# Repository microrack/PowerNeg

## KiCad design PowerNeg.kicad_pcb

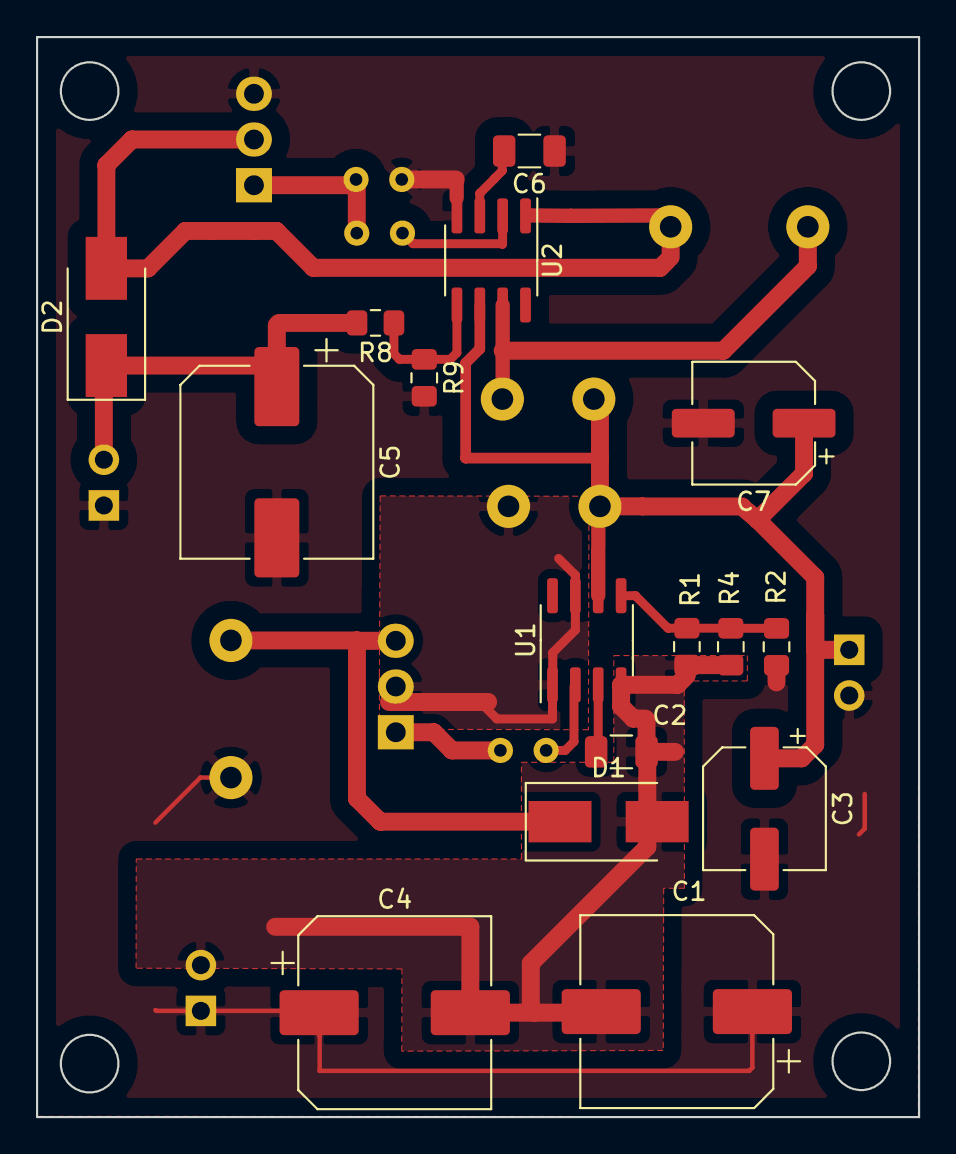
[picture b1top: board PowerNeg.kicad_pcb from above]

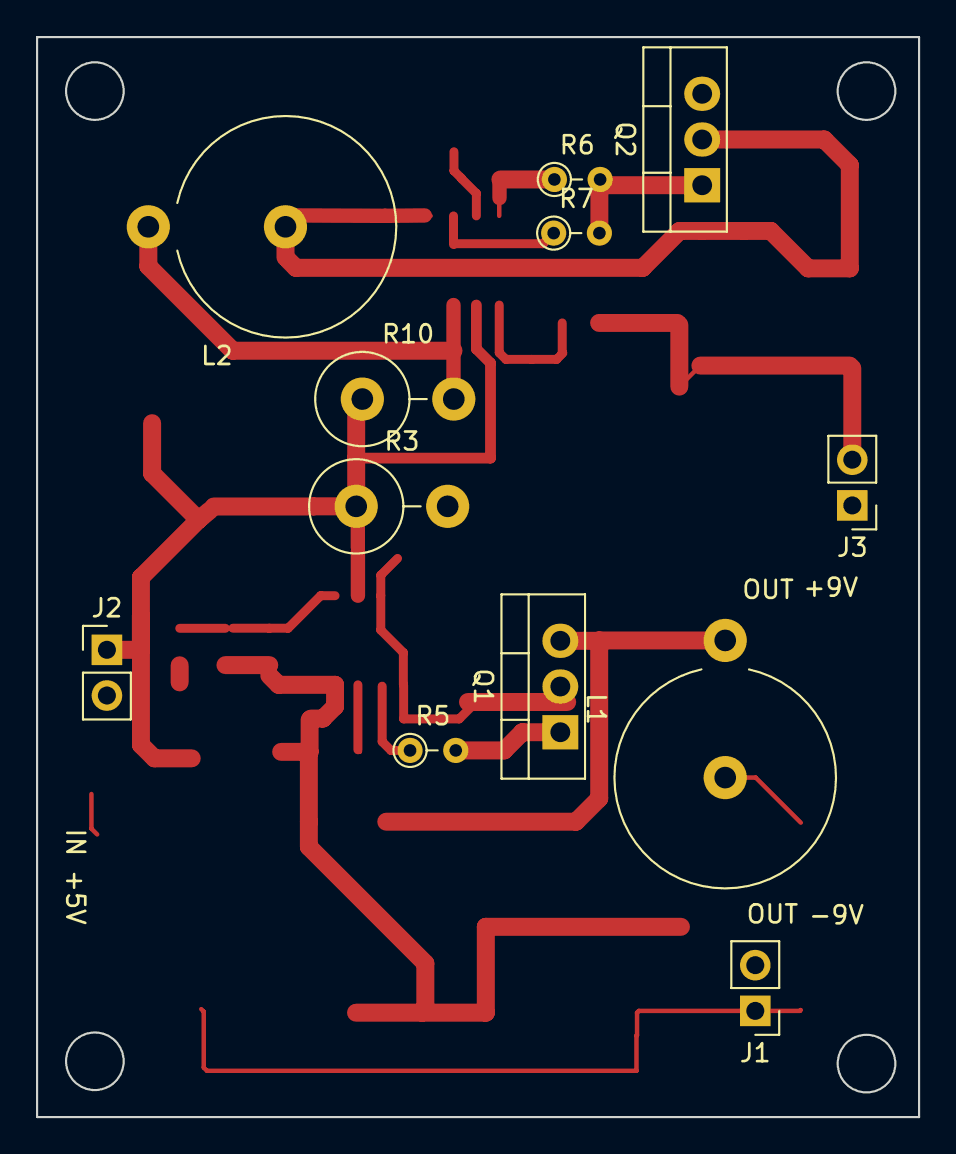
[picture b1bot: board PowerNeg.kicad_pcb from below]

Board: 2 copper layers, 49.0 x 60.0 mm, 28 parts (12 on the bottom side), 16 nets.

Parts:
C1, C4, C5: 1000 uf; CP_Elec_10x10.5
C2: 4.8 pf; C_1206
C3, C7: 100 uf; CP_Elec_6.3x5.4
C6: 2.2 nf; C_1206
D1, D2: D; D_SMB_Handsoldering
J1, J2, J3: Conn_01x02_Male; PinHeader_1x02_P2.54mm_Vertical
L1, L2: L; L_Axial_L20.3mm_D12.1mm_P7.62mm_Vertical_Vishay_IHA-101
Q1, Q2: TIP41C; TO-220-3_Vertical
R1: 1 k; R_0805_2012Metric_Pad1.15x1.40mm_HandSolder
R2: 8.2 k; R_0805_2012Metric_Pad1.15x1.40mm_HandSolder
R3, R10: 0.24R; R_Axial_DIN0516_L15.5mm_D5.0mm_P5.08mm_Vertical
R4: 20 k; R_0805_2012Metric_Pad1.15x1.40mm_HandSolder
R5, R7: 1 k; R_Axial_DIN0204_L3.6mm_D1.6mm_P2.54mm_Vertical
R6: 10 k; R_Axial_DIN0204_L3.6mm_D1.6mm_P2.54mm_Vertical
R8: 47 k; R_0805_2012Metric_Pad1.15x1.40mm_HandSolder
R9: 22 k; R_0805_2012Metric_Pad1.15x1.40mm_HandSolder
U1, U2: MCP3063; SOIC-8_3.9x4.9mm_P1.27mm

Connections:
+5V: C3.1, C7.1, J2.1, R3.1, R10.1, U1.6, U2.6
+9V: C5.1, D2.1, J3.2, R8.2
-9V: C1.2, C2.1, C4.2, D1.2, J1.2, R1.2, R4.2, U1.4
GND: C1.1, C3.2, C4.1, C5.2, C6.1, C7.2, J1.1, J2.2, J3.1, L1.1, Q2.3, R2.2, R6.1, R9.2, U2.4
unnamed: C2.2, U1.3
unnamed: C6.2, U2.3
unnamed: D1.1, L1.2, Q1.3
unnamed: D2.2, L2.1, Q2.2, U2.1
unnamed: L2.2, R10.2, U2.7
unnamed: Q1.1, R5.2
unnamed: Q1.2, R3.2, U1.1, U1.7
unnamed: Q2.1, R6.2, R7.2
unnamed: R1.1, R2.1, R4.1, U1.5
unnamed: R5.1, U1.2
unnamed: R7.1, U2.2
unnamed: R8.1, R9.1, U2.5

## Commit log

2020-12-04 First test versiont negativ power stepup converter
2020-12-15 add positiv power source edited PCB
